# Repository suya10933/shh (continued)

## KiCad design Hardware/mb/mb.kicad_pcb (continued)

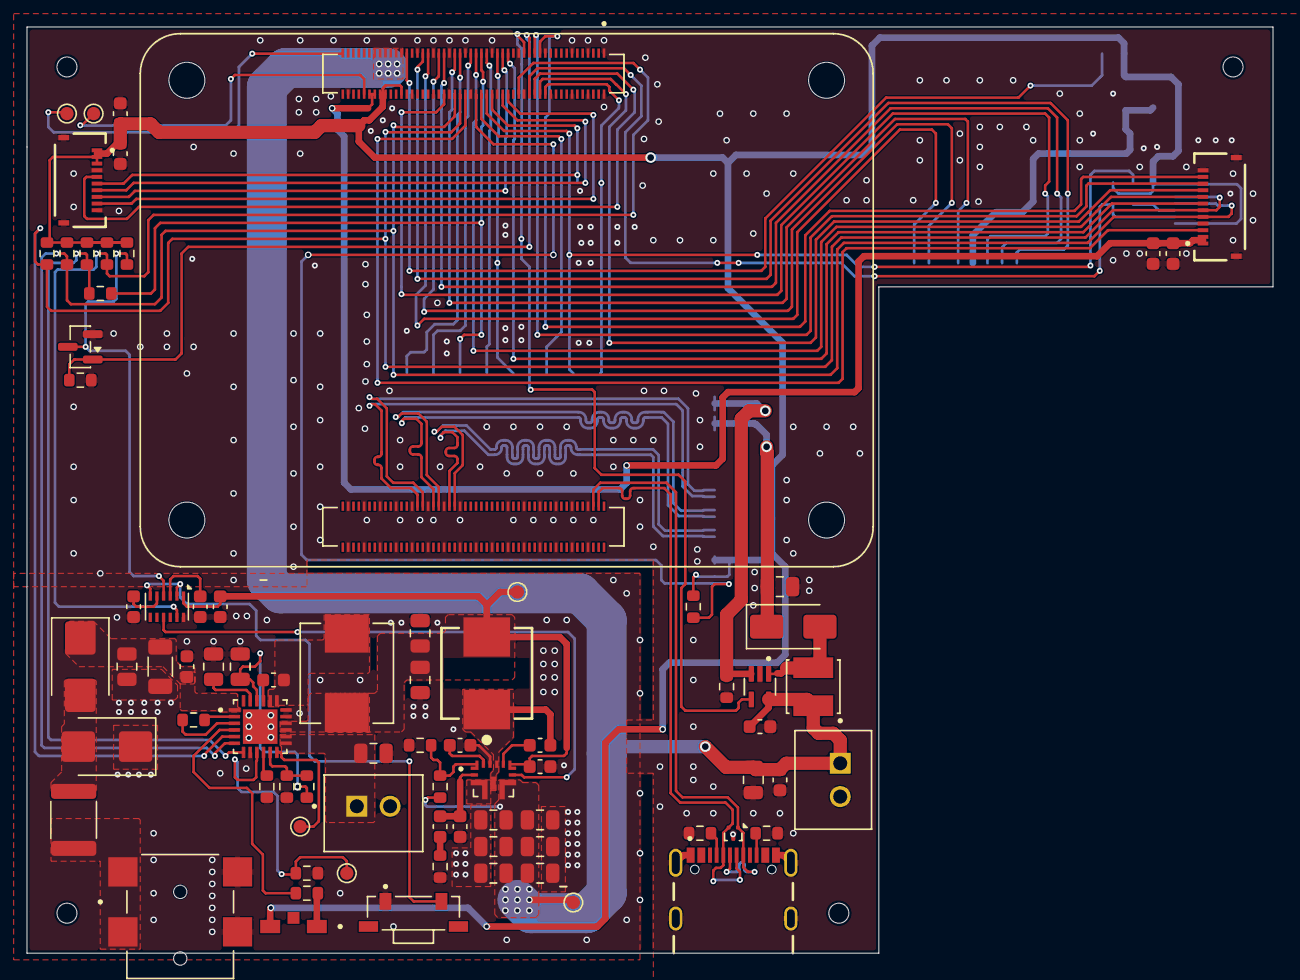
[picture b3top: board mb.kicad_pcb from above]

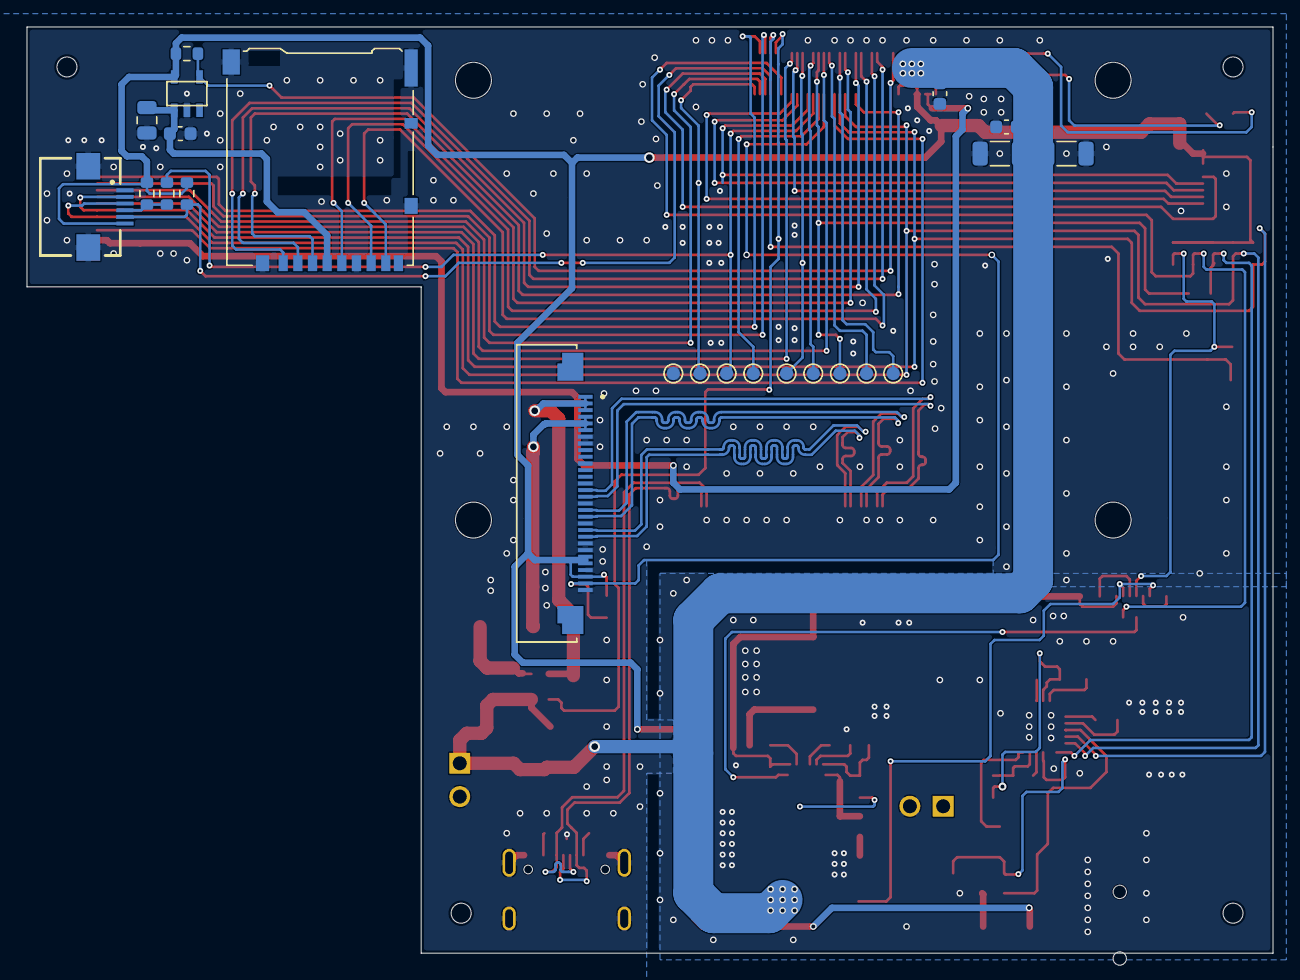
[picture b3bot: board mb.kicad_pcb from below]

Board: 4 copper layers, 93.5 x 69.5 mm, 102 parts (23 on the bottom side), 83 nets.

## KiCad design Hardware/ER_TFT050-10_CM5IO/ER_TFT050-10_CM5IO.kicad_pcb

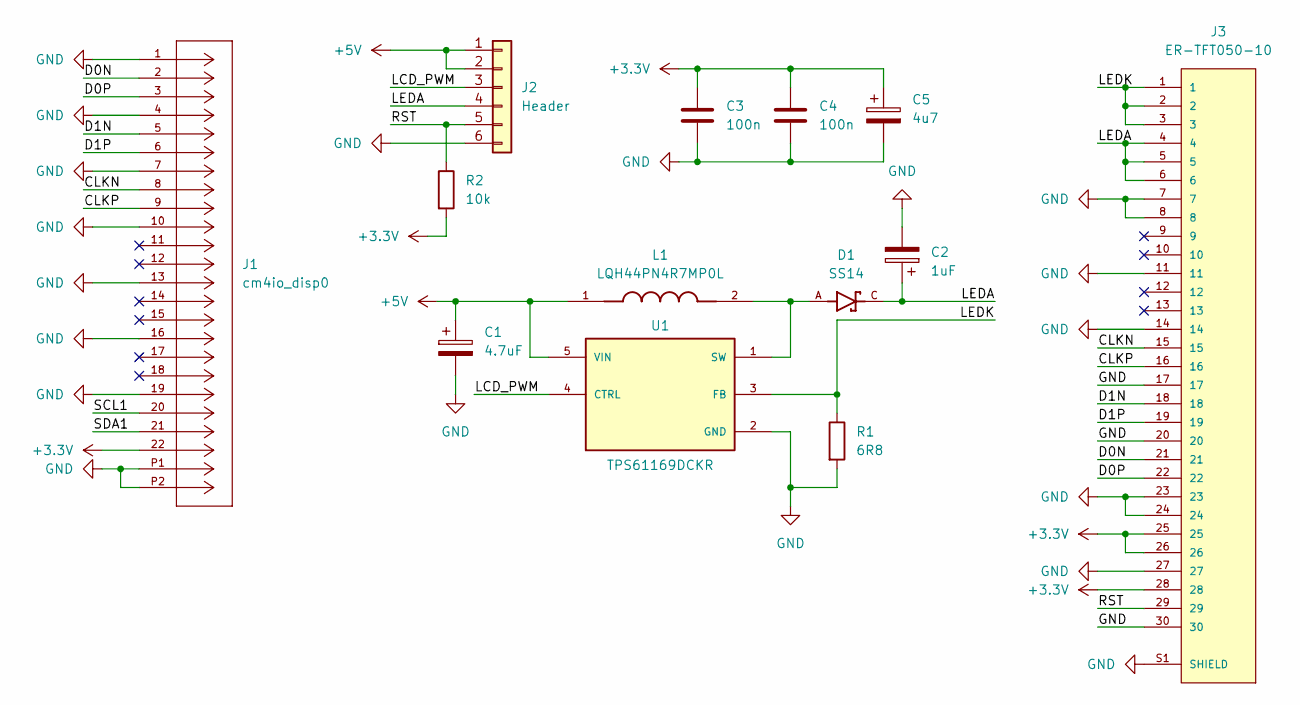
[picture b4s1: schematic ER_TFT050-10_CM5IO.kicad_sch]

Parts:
C1: 4.7uF; CAPC1608X90N
C2: 1uF; CAPC2012X140N
C3, C4: 100n; C_0805_2012Metric_Pad1.18x1.45mm_HandSolder
C5: 4u7; CP_EIA-7343-30_AVX-N_HandSolder
D1: SS14; DIOM4325X250N; PARTREV O2102
J1: cm4io_disp0; CON_5034802200_MOL; MANUFACTURER_PART_NUMBER 5034802200
J2: Header; PinHeader_2x03_P2.54mm_Vertical
J3: ER-TFT050-10; HIROSE_FH12-30S-0.5SH_55_
L1: LQH44PN4R7MP0L; IND_LQH44PN4R7MP0L; PARTREV N/A
R1: 6R8; R_0805_2012Metric_Pad1.20x1.40mm_HandSolder
R2: 10k; R_0805_2012Metric_Pad1.20x1.40mm_HandSolder
U1: TPS61169DCKR; SOT65P210X110-5N; PARTREV A

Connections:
+3.3V: C3.1, C4.1, C5.1, J1.22, J3.25, J3.26, J3.28, R2.2
+5V: C1.1, J2.1, J2.2, L1.1, U1.5 (VIN)
/CLKN: J1.8, J3.15
/CLKP: J1.9, J3.16
/D0N: J1.2, J3.21
/D0P: J1.3, J3.22
/D1N: J1.5, J3.18
/D1P: J1.6, J3.19
/LCD_PWM: J2.3, U1.4 (CTRL)
/LEDA: C2.1, D1.C, J2.4, J3.4, J3.5, J3.6
/LEDK: J3.1, J3.2, J3.3, R1.1, U1.3 (FB)
/RST: J2.5, J3.29, R2.1
/SCL1: J1.20
/SDA1: J1.21
GND: C1.2, C2.2, C3.2, C4.2, C5.2, J1.1, J1.4, J1.7, J1.10, J1.13, J1.16, J1.19, J1.P1, J1.P2, J2.6, J3.7, J3.8, J3.11, J3.14, J3.17, J3.20, J3.23, J3.24, J3.27, J3.30, J3.S1 (SHIELD), J3.S2 (SHIELD), R1.2, U1.2 (GND)
unnamed: D1.A, L1.2, U1.1 (SW)

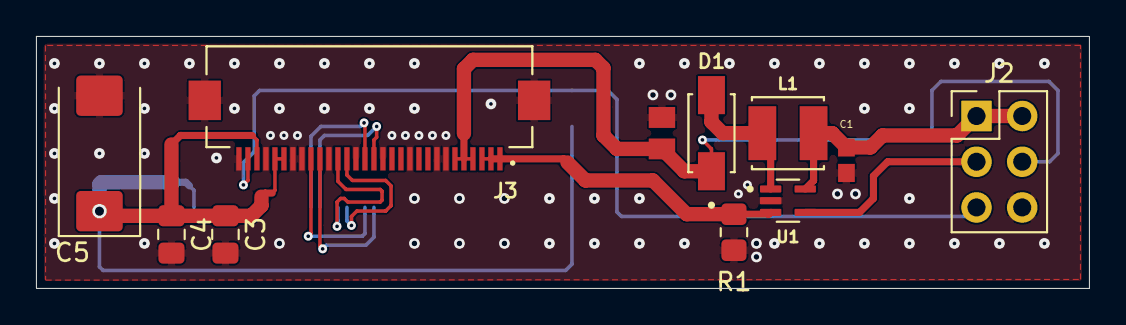
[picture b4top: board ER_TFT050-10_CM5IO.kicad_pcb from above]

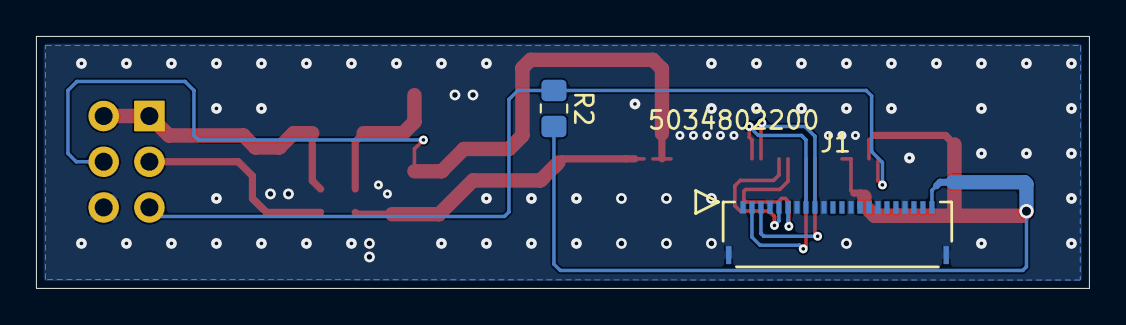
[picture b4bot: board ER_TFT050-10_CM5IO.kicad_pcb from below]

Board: 2 copper layers, 58.5 x 14.0 mm, 13 parts (2 on the bottom side), 14 nets.

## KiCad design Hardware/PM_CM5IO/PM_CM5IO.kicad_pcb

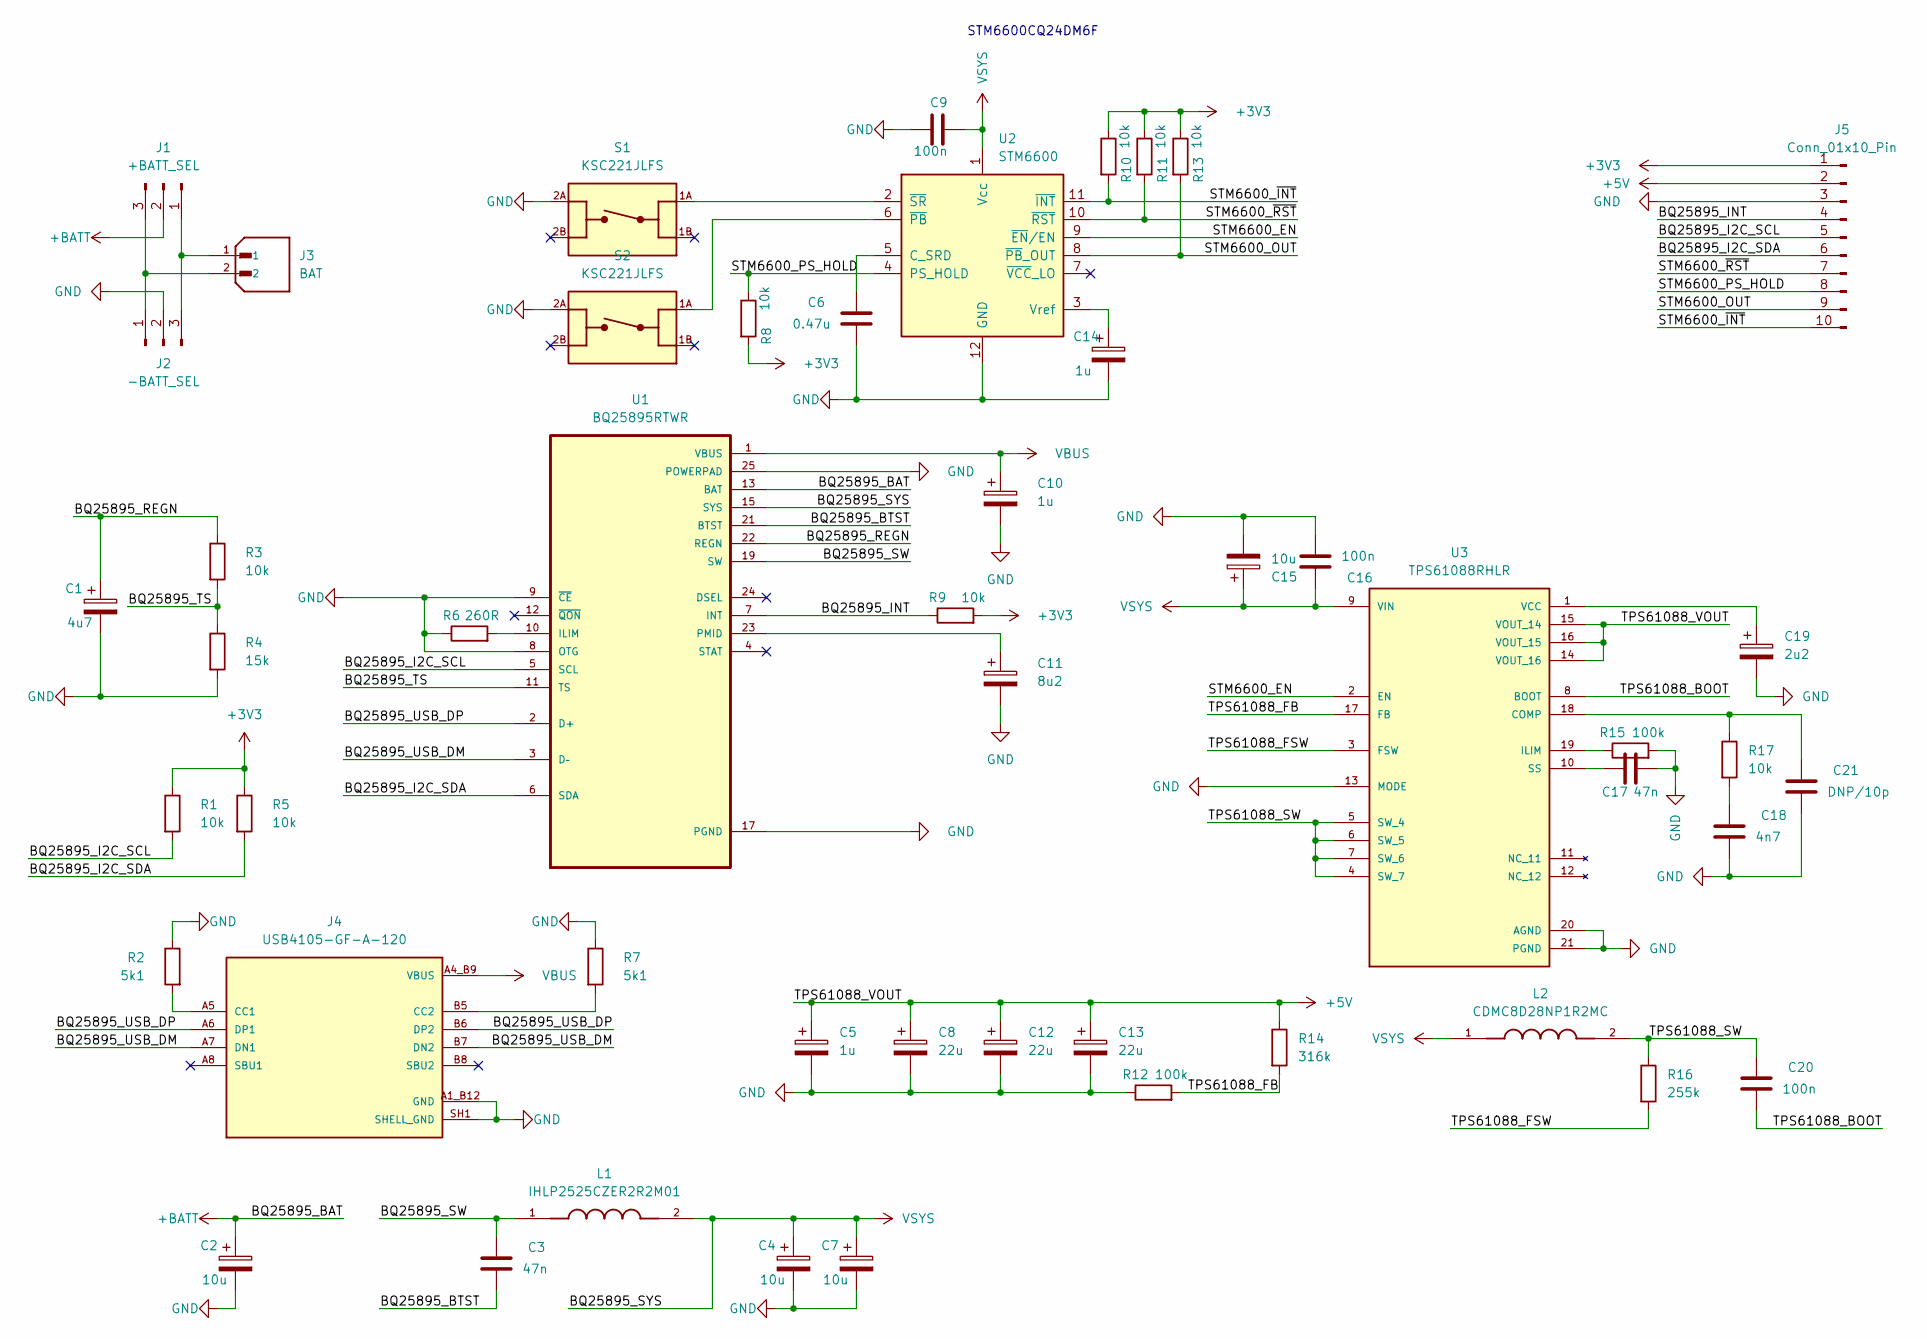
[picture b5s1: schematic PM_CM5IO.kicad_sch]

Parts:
C1: 4u7; CP_EIA-3216-10_Kemet-I_HandSolder
C2, C4, C7, C15: 10u; CP_EIA-3216-10_Kemet-I_HandSolder
C3, C17: 47n; C_0805_2012Metric_Pad1.18x1.45mm_HandSolder
C5, C10, C14: 1u; CP_EIA-3216-10_Kemet-I_HandSolder
C6: 0.47u; C_0805_2012Metric_Pad1.18x1.45mm_HandSolder
C8, C12, C13: 22u; CP_EIA-3216-10_Kemet-I_HandSolder
C9, C16, C20: 100n; C_0805_2012Metric_Pad1.18x1.45mm_HandSolder
C11: 8u2; CP_EIA-3216-10_Kemet-I_HandSolder
C18: 4n7; C_0805_2012Metric_Pad1.18x1.45mm_HandSolder
C19: 2u2; CP_EIA-3216-10_Kemet-I_HandSolder
C21: DNP/10p; C_0805_2012Metric_Pad1.18x1.45mm_HandSolder
J1: +BATT_SEL; PinHeader_1x03_P2.54mm_Vertical
J2: -BATT_SEL; PinHeader_1x03_P2.54mm_Vertical
J3: BAT; JST_B2B-XH-A_LF__SN_; PARTREV N/A
J4: USB4105-GF-A-120; GCT_USB4105-GF-A-120; PARTREV B3
J5: Conn_01x10_Pin; PinHeader_1x10_P2.54mm_Vertical
L1: IHLP2525CZER2R2M01; INDM686X647X300N; PARTREV 16-Oct-2020
L2: CDMC8D28NP1R2MC; IND_CDMC8D28NP1R2MC; PARTREV 10-Jan-17
R1, R3, R5, R8, R9, R10, R11, R13, R17: 10k; R_0805_2012Metric_Pad1.20x1.40mm_HandSolder
R2, R7: 5k1; R_0805_2012Metric_Pad1.20x1.40mm_HandSolder
R4: 15k; R_0805_2012Metric_Pad1.20x1.40mm_HandSolder
R6: 260R; R_0805_2012Metric_Pad1.20x1.40mm_HandSolder
R12, R15: 100k; R_0805_2012Metric_Pad1.20x1.40mm_HandSolder
R14: 316k; R_0805_2012Metric_Pad1.20x1.40mm_HandSolder
R16: 255k; R_0805_2012Metric_Pad1.20x1.40mm_HandSolder
S1, S2: KSC221JLFS; SW_KSC221JLFS; PARTREV 16 Mar 22
U1: BQ25895RTWR; QFN50P400X400X80-25N
U2: STM6600; TDFN-12_2x3mm_P0.5mm
U3: TPS61088RHLR; IC_TPS61088RHLR; PARTREV 4219071/A 05/2017

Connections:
+3V3: J5.1, R1.1, R5.1, R8.2, R9.2, R10.1, R11.1, R13.1
+5V: C5.1, C8.1, C12.1, C13.1, J5.2, R14.1, U3.14 (VOUT_16), U3.15 (VOUT_14), U3.16 (VOUT_15)
+BATT: C2.1, J1.2, U1.13 (BAT), U1.14 (BAT)
/BQ25895_BTST: C3.2, U1.21 (BTST)
/BQ25895_I2C_SCL: J5.5, R1.2, U1.5 (SCL)
/BQ25895_I2C_SDA: J5.6, R5.2, U1.6 (SDA)
/BQ25895_INT: J5.4, R9.1, U1.7 (INT)
/BQ25895_REGN: C1.1, R3.1, U1.22 (REGN)
/BQ25895_TS: R3.2, R4.1, U1.11 (TS)
/BQ25895_USB_DM: J4.A7 (DN1), J4.B7 (DN2), U1.3 (D–)
/BQ25895_USB_DP: J4.A6 (DP1), J4.B6 (DP2), U1.2 (D+)
/STM6600_EN: U2.9 (~EN/EN), U3.2 (EN)
/STM6600_OUT: J5.9, R13.2, U2.8 (~PB_OUT)
/STM6600_PS_HOLD: J5.8, R8.1, U2.4 (PS_HOLD)
/STM6600_~INT: J5.10, R10.2, U2.11 (~INT)
/STM6600_~RST: J5.7, R11.2, U2.10 (~RST)
/TPS61088_BOOT: C20.2, U3.8 (BOOT)
/TPS61088_FB: R12.2, R14.2, U3.17 (FB)
/TPS61088_FSW: R16.2, U3.3 (FSW)
/TPS61088_SW: C20.1, L2.2, R16.1, U3.4 (SW_7), U3.5 (SW_4), U3.6 (SW_5), U3.7 (SW_6)
GND: C1.2, C2.2, C4.2, C5.2, C6.2, C7.2, C8.2, C9.1, C10.2, C11.2, C12.2, C13.2, C14.2, C15.2, C16.2, C17.2, C18.2, C19.2, C21.2, J2.2, J4.A1_B12 (GND), J4.B1_A12 (GND), J4.SH1 (SHELL_GND), J4.SH2 (SHELL_GND), J4.SH3 (SHELL_GND), J4.SH4 (SHELL_GND), J5.3, R2.1, R4.2, R6.1, R7.1, R12.1, R15.2, S1.2A, S2.2A, U1.8 (OTG), U1.9 (~CE), U1.17 (PGND), U1.18 (PGND), U1.25 (POWERPAD), U2.12 (GND), U3.13 (MODE), U3.20 (AGND), U3.21 (PGND), U3.22 (PGND), U3.23 (PGND), U3.24 (PGND), U3.25 (PGND), U3.26 (PGND), U3.27 (PGND), U3.28 (PGND), U3.29 (PGND)
unnamed: C18.1, R17.2
unnamed: J1.1, J2.3, J3.1
unnamed: J1.3, J2.1, J3.2
unnamed: J4.A5 (CC1), R2.2
unnamed: J4.B5 (CC2), R7.2
unnamed: R6.2, U1.10 (ILIM)
unnamed: C11.1, U1.23 (PMID)
unnamed: C6.1, U2.5 (C_SRD)
unnamed: C14.1, U2.3 (Vref)
unnamed: S2.1A, U2.6 (~PB)
unnamed: S1.1A, U2.2 (~SR)
unnamed: C21.1, R17.1, U3.18 (COMP)
unnamed: R15.1, U3.19 (ILIM)
unnamed: C17.1, U3.10 (SS)
unnamed: C19.1, U3.1 (VCC)
SW: C3.1, L1.1, U1.19 (SW), U1.20 (SW)
VBUS: C10.1, J4.A4_B9 (VBUS), J4.B4_A9 (VBUS), U1.1 (VBUS)
VSYS: C4.1, C7.1, C9.2, C15.1, C16.1, L1.2, L2.1, U1.15 (SYS), U1.16 (SYS), U2.1 (Vcc), U3.9 (VIN)

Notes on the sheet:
STM6600CQ24DM6F

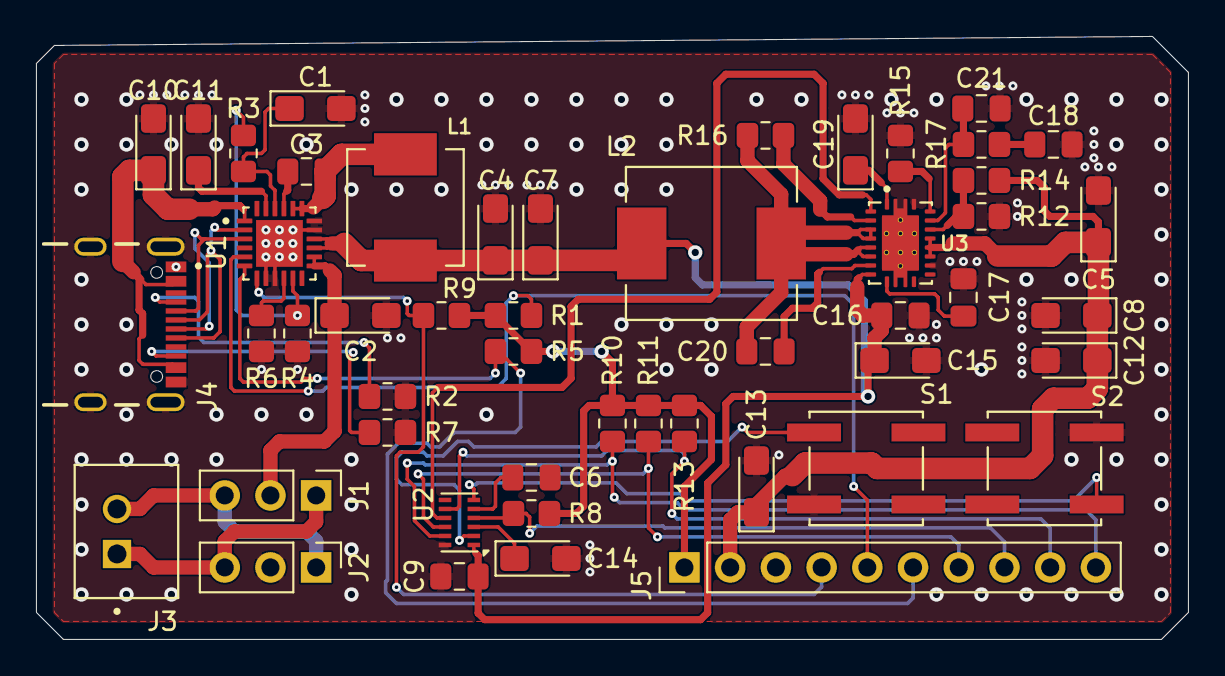
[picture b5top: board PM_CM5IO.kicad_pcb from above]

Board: 2 copper layers, 64.0 x 33.5 mm, 50 parts (0 on the bottom side), 39 nets.

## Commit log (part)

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2026-06-15 init
2026-06-15 kicad lib
2026-06-15 pm_cm5io lib table
